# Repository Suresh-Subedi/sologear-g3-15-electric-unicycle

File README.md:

# Sologear G3-15 Electric Unicycle
Sologear G3-15 Electric Unicycle reverse engineering to reuse motherboard with custom firmware.
Schematics of other generic cheaper electric unicycles (monowheels) should be same/similar. Let us know in the issues.

### Running code
Install Platform IO extension in VS Code.
Open firmware folder in VS Code
Connect programmer (without connecting 3.3V)
Switch monowheel on

Monowheel folder contains KiCad files for the monowheel.

### Ports
#### P2
|Pin|Marking|Comment      |
|---|-------|-------------|
|1  |5V     |             |
|2  |       |Not connected|
|3  |SPK    |             |

Connected in parallel with buzzer

#### P3 Power switch LED
|Pin|Marking|Comment|
|---|-------|-------|
|1  |       |5V     |
|2  |       |       |
|3  |       |       |

#### P4 Hall sensor
|STM32F103C8T6|Hall sensor|Color |Comment        |
|-------------|-----------|------|---------------|
|             |1          |Black |GND            |
|PA0          |2          |Blue  |               |
|PA1          |3          |Yellow|               |
|PA2          |4          |Green |               |
|             |5          |Red   |5V              |

#### P5 Battery indicator
From switch to charging connector: 1 - 4
|STM32F103C8T6|P4 Battery Indicator|Color |Comment        |
|-------------|--------------------|------|---------------|
|PA15         |1                   |Black |Via resistor R1|
|PB4          |2                   |Blue  |Via resistor R2|
|PB5          |3                   |Yellow|Via resistor R3|
|PB8          |4                   |Green |Via resistor R4|
|             |5                   |Red   |+5V            |

#### P6
|Pin|Marking|Comment|
|---|-------|-----------------------|
|1  |       |PA4 via R6 10k resistor|
|2  |       |GND                    |

#### P7 Power switch ON OFF PWR
|Pin|Marking|Comment      |
|---|-------|-------------|
|1  |       |+60V         |
|2  |       |To board     |

#### SWD
|STM32F103C8T6|SWD|
|-------------|---|
|PA14         |SWC|
|PA13         |SWD|
|             |3V3|
|             |GND|

[Bill of materials](https://docs.google.com/spreadsheets/d/1EM--kQIaX84T2JI6LrDOyGJttcWCDYOLsfqfUfqGejQ/edit?usp=sharing)

|Step|1   |2   |3   |4   |5   |6   |
|----|----|----|----|----|----|----|
|High|A   |B   |B   |C   |C   |A   |
|Low |C   |C   |A   |A   |B   |B   |
|    |H1L3|H2L3|H2L1|H3L1|H3L2|H1L2|

https://www.digikey.be/nl/articles/what-is-the-most-effective-way-to-commutate-a-bldc-motor
https://www.digikey.nl/en/blog/using-bldc-hall-sensors-as-position-encoders-part-1
| |U  |V  |W  |Step|
|-|---|---|---|----|
|1|+  |-  |off|6   |
|2|+  |off|-  |1   |
|3|off|+  |-  |2   |
|4|-  |+  |off|3   |
|5|-  |off|+  |4   |
|6|off|-  |+  |5   |
| |A  |B  |C  |    |

#### Connections
|STM32F103C8T6|MPU 6050|Comment         |
|-------------|--------|----------------|
|PB7          |SDA     |Via resistor R31|
|PB6          |SCL     |Via resistor R33|

Half-Bridge Driver connections
|STM32F103C8T6|IRS2108 |
|-------------|--------|
|PB10         |HIN1    |
|PB09         |HIN2    |
|PB08         |HIN3    |
|PB15         |LIN1    |
|PB14         |LIN2    |
|PB13         |LIN3    |

### Firmware
Existing firmware was unprotected and could be read using STM-Link V2. Soldering headers was a bit difficult as pin holes were already filled with solder.

### Components
STM32F103C8T6\
InvenSense MPU 6050\
6 MOSFET ST P75NF75&\
[IRS2108 Half-bridge Driver](https://www.infineon.com/dgdl/irs2108.pdf?fileId=5546d462533600a40153567649d627a8) 8-Lead SOIC

### Battery
59.2V/4.4Ah 260Wh SAMSUNG/22PM\
Hy-LYX-1602B-22PM-144900042

### Motor
CST e-BIKE PRO Li-ion Electronic\
14AMK1512615052\
XINAOMA

### Useful software
STM32 ST-LINK Utility\
Ghidra with SVD-Loader

### Connections
|Marking on board|Connections|Connected                    |
|----------------|-----------|-----------------------------|
|P2              |2          |5v SPK Unpopulated           |
|P3              |3          |2p connected to switch LED   |
|P4              |5          |2mm: battery level           |
|P5              |5          |2.5mm: hall effect sensor    |
|P6              |2          |Disconnected                 |
|P7              |2          |Switch                       |
#### Switch
|Marking on board|Color|Switch|
|----------------|-----|------|
|P3              |Red  |      |
|P3              |Black|      |
|P7              |Red  |      |
|P7              |White|Center|

#### Charging port
Red
Black
Connected to battery
#### Motor connection
|Color |Marking on board|
|------|----------------|
|Yellow|Y?              |
|Green |V               |
|Blue  |W               |

???
GND
3.3V

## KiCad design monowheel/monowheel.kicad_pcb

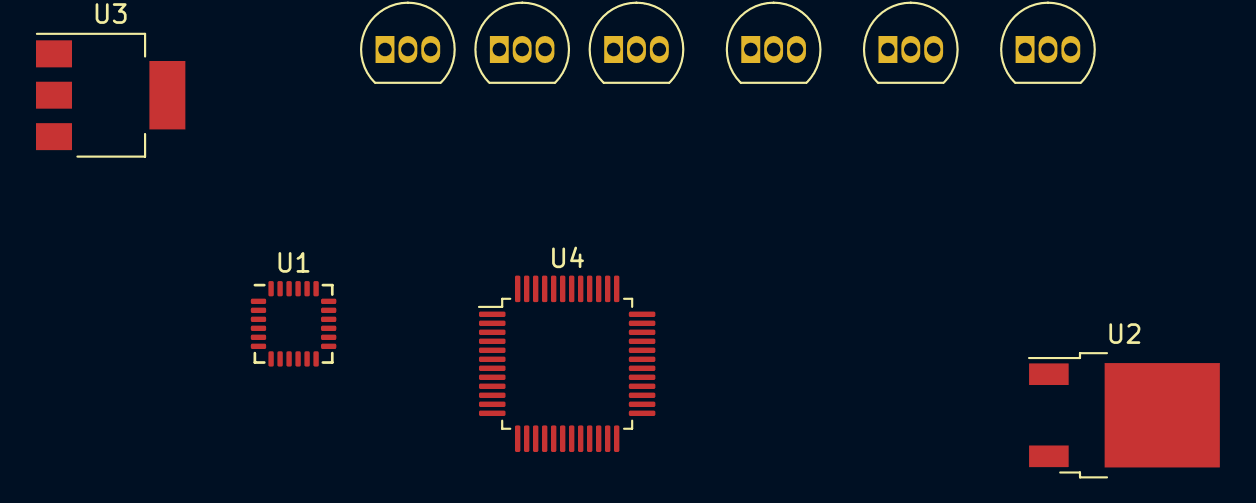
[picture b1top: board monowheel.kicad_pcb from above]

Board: 2 copper layers, 10 parts (0 on the bottom side), 5 nets, no tracks yet.

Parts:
Q6, Q7, Q8, Q9, Q10, Q11: 75F75; TO-92_Inline
U1: MPU-6050; InvenSense_QFN-24_4x4mm_P0.5mm
U2: LM78M05_TO252; TO-252-2
U3: AP1117-33; SOT-223-3_TabPin2
U4: STM32F103C6Tx; LQFP-48_7x7mm_P0.5mm

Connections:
/U: Q10.1 (S), Q11.3 (D)
/V: Q8.1 (S), Q9.3 (D)
/W: Q6.1 (S), Q7.3 (D)
unnamed: Q7.1 (S), Q9.1 (S), Q11.1 (S)
unnamed: Q6.3 (D), Q8.3 (D), Q10.3 (D)

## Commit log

2022-07-28 Update README.md
    formatting
2022-07-31 include images in repo
2022-08-01 add more info to schema
2022-08-01 fixes
2022-08-05 improvements
2022-08-05 add specs 4 caps
2022-08-12 add platformio code
2022-08-12 proper names
2022-10-21 add kicad files
2023-02-01 add code to control buzzer and leds
